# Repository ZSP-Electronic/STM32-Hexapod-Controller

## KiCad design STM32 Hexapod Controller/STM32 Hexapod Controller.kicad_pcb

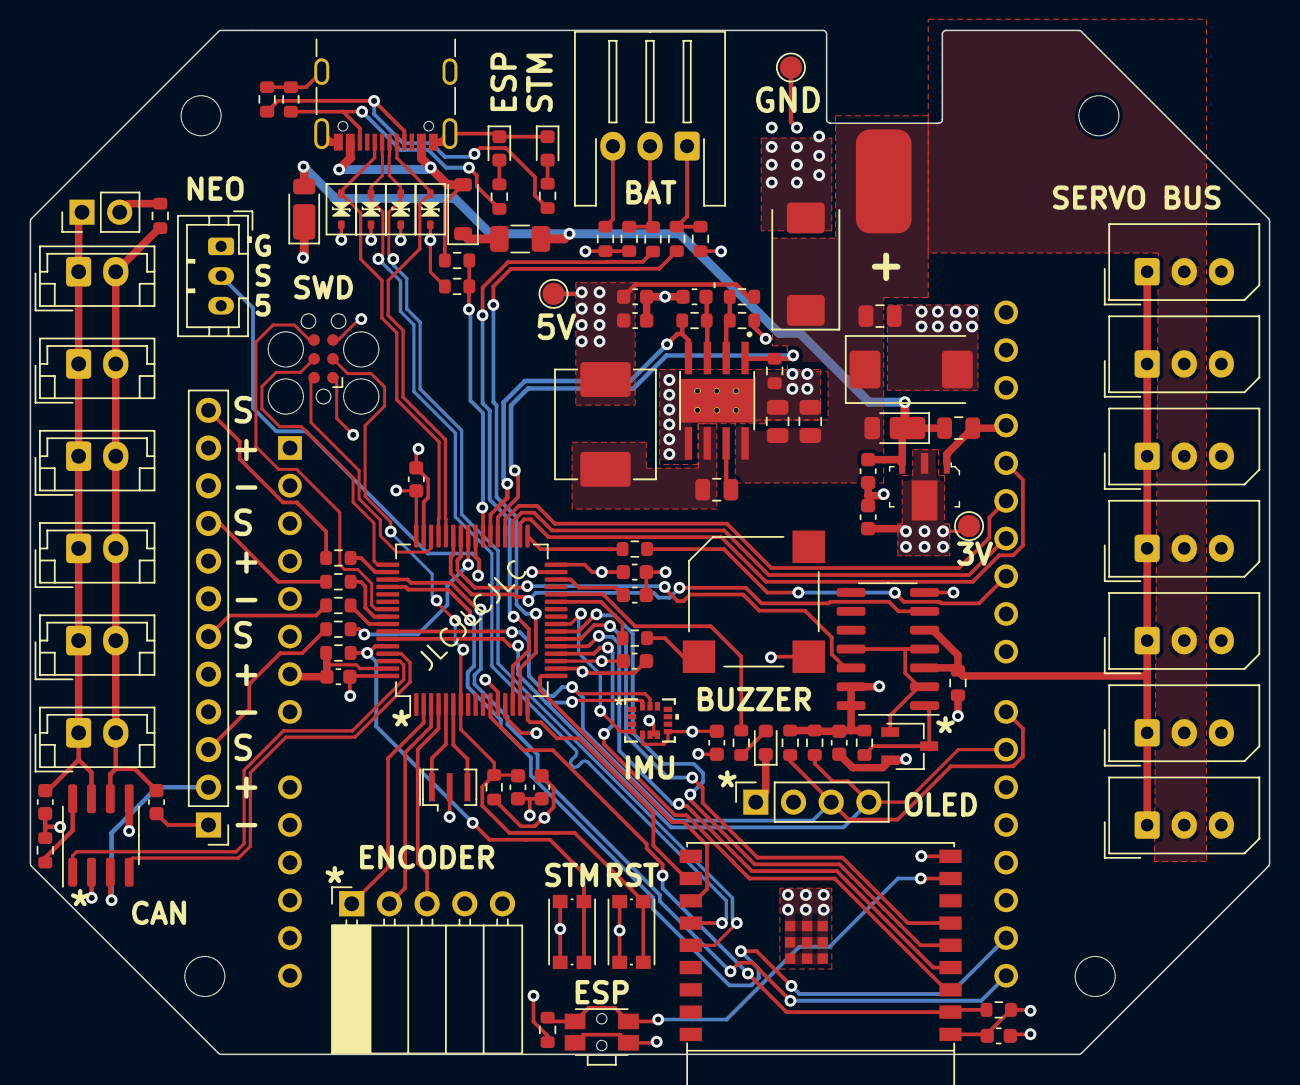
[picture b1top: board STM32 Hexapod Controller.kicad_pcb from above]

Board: 4 copper layers, 83.5 x 69.0 mm, 111 parts (1 on the bottom side), 80 nets.

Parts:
A1: Arduino_UNO_R3
BZ1: Buzzer; MagneticBuzzer_Kobitone_254-EMB84Q-RO
C1, C2: 100uF; CP_EIA-7343-31_Kemet-D
C3: 10u; C_0805_2012Metric
C4, C38, C39, C40, C41, C42, C45, C46: 10uF; C_0603_1608Metric
C6, C7, C13: 10uF; C_0805_2012Metric
C8: .1uF; C_0805_2012Metric
C9, C10, C14: 22uF; C_0603_1608Metric
C11: .47uF; C_0603_1608Metric
C12: 1uF; C_0603_1608Metric
C35, C37: 47pF; C_0603_1608Metric
C47: 1nF; C_0603_1608Metric
C48: 4.7uF; C_0603_1608Metric
D1: 1N914WT; D_SOD-123
D2: STM; LED_0603_1608Metric
D3, D4, D5, D6: DESD5V0U1BA; D_SOD-323_TVS
D7, D10: D_Small; D_PowerDI-123
D8: ESP; LED_0603_1608Metric
D9: LED; LED_0603_1608Metric
F1: Polyfuse_Small; Fuse_1206_3216Metric
H1, H2, H3, H4: MountingHole; MountingHole_2.7mm_M2.5
J1, J2, J3, J4, J5, J6, J18: Conn_01x03_Socket; Molex_SPOX_5267-03A_1x03_P2.50mm_Vertical
J7: Conn_01x03; JST_XH_S3B-XH-A-1_1x03_P2.50mm_Horizontal
J8: USB_C_Receptacle_USB2.0; USB_C_Receptacle_GCT_USB4105-xx-A_16P_TopMnt_Horizontal
J9, J10, J11, J12, J13, J14: Conn_01x02_Socket; JST_EH_B2B-EH-A_1x02_P2.50mm_Vertical
J15: Conn_ARM_SWD_TagConnect_TC2030; Tag-Connect_TC2030-IDC-FP_2x03_P1.27mm_Vertical
J16: Conn_01x02_Pin; PinHeader_1x02_P2.54mm_Vertical
J17: Conn_01x12_Pin; PinHeader_1x12_P2.54mm_Vertical
J19: Conn_01x03_Socket; JST_PH_B3B-PH-K_1x03_P2.00mm_Vertical
J20: Conn_01x05_Socket; PinSocket_1x05_P2.54mm_Horizontal
J21: Conn_01x04_Socket; PinSocket_1x04_P2.54mm_Vertical
L1: 3.3uH; L_Abracon_ASPI-0630LR
P1: CONN_002; DEAN_PCB
Q1: 2N7002AQ; TSOT-23
R1, R2, R4, R21, R25, R26, R33: 1K; R_0603_1608Metric
R3, R10: 1K5; R_0603_1608Metric
R5: DNP; R_0603_1608Metric
R6: 3K; R_0603_1608Metric
R7, R8, R18, R19, R20, R23, R28, R29, R30: 10K; R_0603_1608Metric
R9: 11K5; R_0603_1608Metric
R11: 100K; R_0603_1608Metric
R12, R13, R14, R15, R24: 100R; R_0603_1608Metric
R16, R17: 5.1K; R_0603_1608Metric
R22: 120R; R_0603_1608Metric
R31, R32: 4K7; R_0603_1608Metric
SW1, SW2: SW_Push; SW_Push_1P1T_NO_CK_KMR2
SW3: SW_Push; SW_SPST_EVQP7C
TP1, TP2, TP3: TestPoint; TestPoint_Pad_D1.5mm
U1: 74126; SOIC-14_3.9x8.7mm_P1.27mm
U2: TPS56528DDAR; IC_TPS56528DDAR
U3: AZ1117CH-3_3TRG1; TO-243AA
U4: ESP32-C3-WROOM-02
U5: STM32F446RETx; LQFP-64_10x10mm_P0.5mm
U6: TJA1051T-3; SOIC-8_3.9x4.9mm_P1.27mm
U7: LSM6DSOTR; LGA-14L_2P5X3X0P86_STM
Y1: Resonator_Small; Resonator_SMD_Murata_CSTxExxV-3Pin_3.0x1.1mm

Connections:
+3.3V: C4.1, C14.1, C38.1, C39.1, C40.1, C41.1, C42.1, C45.1, C46.1, J15.1 (VCC), J20.4, J21.2, R1.1, R2.1, R18.1, R20.1, R30.1, R31.1, R32.1, SW2.1, TP3.1, U1.13 (EN), U1.14 (VCC), U3.2 (OUT), U3.4 (VOUT), U4.1 (3V3), U5.13 (VDDA), U5.19 (VDD), U5.32 (VDD), U5.48 (VDD), U5.64 (VDD), U6.5 (VIO), U7.5 (VDDIO), U7.8 (VDD)
/+5V: A1.5 (+5V), A1.8 (VIN), C9.1, C10.1, D7.1 (K), J17.2, J17.5, J17.8, J17.11, J19.3, L1.2, R9.1, TP1.1, U6.3 (VCC)
/+12V: C1.1, C2.1, C3.1, C6.1, C7.1, D10.2 (A), J1.2, J2.2, J3.2, J4.2, J5.2, J6.2, J18.2, P1.1, U2.8 (VIN)
/BAT1: R3.1, U5.15 (PA1)
/BAT2: R6.1, U5.14 (PA0)
/CAN_HIGH: C35.2, J9.1, J10.1, J11.1, J12.1, J13.1, J14.1, J16.1, U6.7 (CANH)
/CAN_LOW: C37.1, J9.2, J10.2, J11.2, J12.2, J13.2, J14.2, R22.2, U6.6 (CANL)
/CAN_RX: U5.61 (PB8), U6.4 (RXD)
/CAN_SILENT: R23.1, U6.8 (S)
/CAN_TX: U5.62 (PB9), U6.1 (TXD)
/CS: A1.25 (D10), R12.2
/Fan: R24.2, U5.50 (PA15)
/MCU/BUZZER: R21.1, U5.27 (PB1)
/MCU/EN_CLK: J20.1, U5.2 (PC13)
/MCU/EN_DATA: J20.2, U5.3 (PC14)
/MCU/EN_SW: J20.3, U5.4 (PC15)
/MCU/ESP_BOOT: R30.2, SW3.1, U4.8 (GPIO9)
/MCU/ESP_CS: U4.3 (GPIO4/ADC1_CH4), U5.20 (PA4)
/MCU/ESP_MISO: U4.6 (GPIO7), U5.22 (PA6)
/MCU/ESP_MOSI: U4.5 (GPIO6), U5.23 (PA7)
/MCU/ESP_RST: R20.2, U4.2 (EN/CHIP_PU), U5.11 (PC3)
/MCU/ESP_RX_TX: U4.12 (GPIO21/U0TXD), U5.17 (PA3)
/MCU/ESP_SCK: U4.4 (GPIO5/ADC2_CH0), U5.21 (PA5)
/MCU/ESP_TX_RX: U4.11 (GPIO20/U0RXD), U5.16 (PA2)
/MCU/ESP_USB_D+: D5.2 (A), J8.A6 (D+), U4.14 (GPIO19/USB_D+)
/MCU/ESP_USB_D-: D3.2 (A), J8.A7 (D-), U4.13 (GPIO18/USB_D-)
/MCU/IMU_INT: U5.24 (PC4), U7.4 (INT1)
/MCU/LED: R33.1, U5.28 (PB2)
/MCU/REG_EN: R8.2, U2.1 (EN), U5.37 (PC6)
/MCU/REG_PG: R11.1, U2.4 (PG), U5.38 (PC7)
/MCU/RST: C47.1, J15.3 (~RESET), R18.2, SW1.1, U5.7 (NRST)
/MCU/STM_BOOT: R19.1, SW2.2, U5.60 (BOOT0)
/MCU/STM_INPUT: D1.2 (A), J8.A4 (VBUS1), J8.A9 (VBUS2), J8.B4 (VBUS2), J8.B9 (VBUS1), R28.1
/MCU/STM_USB_D+: D6.2 (A), J8.B6 (D+), U5.45 (PA12)
/MCU/STM_USB_D-: D4.2 (A), J8.B7 (D-), U5.44 (PA11)
/MCU/STM_USB_INPUT: R28.2, R29.1, U5.39 (PC8)
/MCU/SWD_CLK: J15.4 (SWCLK), U5.49 (PA14)
/MCU/SWD_DIO: J15.2 (SWDIO), U5.46 (PA13)
/MCU/SWD_SWO: J15.6 (SWO), U5.55 (PB3)
/MISO: A1.27 (D12), U5.36 (PB15)
/MOSI: A1.26 (D11), U5.35 (PB14)
/NEOPIXEL: J19.2, U5.40 (PC9)
/PSU/SW: C8.2, L1.1, U2.6 (SW)
/PSU/VBUS: C12.1, C13.1, D7.2 (A), D10.1 (K), F1.2, U3.3 (IN)
/RX: A1.16 (D1/TX), U5.52 (PC11)
/RX_TX: U1.6 (O), U5.43 (PA10)
/SCK: A1.28 (D13), U5.34 (PB13)
/SCL: A1.22 (D7), J21.3, R31.2, U5.58 (PB6), U7.13 (SCL)
/SDA: A1.21 (D6), J21.4, R32.2, U5.59 (PB7), U7.14 (SDA)
/Servo1: R13.2, U5.41 (PA8)
/Servo2: R14.2, U5.57 (PB5)
/Servo3: R15.2, U5.56 (PB4)
/TX: A1.15 (D0/RX), U5.51 (PC10)
/TX_RX: U1.12 (D), U5.42 (PA9)
/fanc: J17.12, R24.1
/servo1c: J17.3, R13.1
/servo2c: J17.6, R14.1
/servo3: J17.9, R15.1
GND: A1.6 (GND), A1.7 (GND), A1.29 (GND), BZ1.2 (+), C1.2, C2.2, C3.2, C4.2, C6.2, C7.2, C9.2, C10.2, C11.2, C12.2, C13.2, C14.2, C35.1, C37.2, C38.2, C39.2, C40.2, C41.2, C42.2, C45.2, C46.2, C47.2, C48.2, D2.1 (K), D3.1 (K), D4.1 (K), D5.1 (K), D6.1 (K), D8.1 (K), D9.1 (K), J1.3, J2.3, J3.3, J4.3, J5.3, J6.3, J8.A1 (GND), J8.A12 (GND), J8.B1 (GND), J8.B12 (GND), J8.S1 (SHIELD), J15.5 (GND), J17.1, J17.4, J17.7, J17.10, J18.3, J19.1, J20.5, J21.1, P1.2, Q1.2 (S), R4.1, R5.2, R7.1, R8.1, R10.2, R16.2, R17.2, R19.2, R23.2, R29.2, SW1.2, SW3.2, TP2.1, U1.7 (GND), U2.5 (GND), U2.9 (POWERPAD), U3.1 (ADJ/GND), U4.9 (GND), U4.19 (GND), U5.12 (VSSA), U5.18 (VSS), U5.31 (VSS), U5.47 (VSS), U5.63 (VSS), U6.2 (GND), U7.6 (GND), U7.7 (GND), Y1.2
unnamed: BZ1.1 (-), R21.2
unnamed: D1.1 (K), F1.1
unnamed: D2.2 (A), R25.1
unnamed: D8.2 (A), R26.1
unnamed: D9.2 (A), R33.2
unnamed: J7.1, R3.2, R4.2
unnamed: J7.2, R6.2, R7.2
unnamed: J7.3, R5.1
unnamed: J8.A5 (CC1), R17.1, R25.2
unnamed: J8.B5 (CC2), R16.1, R26.2
unnamed: J16.2, R22.1
unnamed: Q1.3 (D), R1.2, U1.1 (EN)
unnamed: Q1.1 (G), U1.2 (D), U1.4 (EN), U1.11 (O)
unnamed: C8.1, U2.7 (VBST)
unnamed: R9.2, R10.1, U2.2 (VFB)
unnamed: C11.1, R11.2, U2.3 (VREG5)
unnamed: R12.1, U5.33 (PB12)
unnamed: U5.5 (PH0), Y1.1
unnamed: U5.6 (PH1), Y1.3
unnamed: C48.1, U5.30 (VCAP_1)
servo: J1.1, J2.1, J3.1, J4.1, J5.1, J6.1, J18.1, R2.2, U1.3 (O), U1.5 (D)

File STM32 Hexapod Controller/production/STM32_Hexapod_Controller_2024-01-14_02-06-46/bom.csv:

Designator,Footprint,Quantity,Value,LCSC Part #
A1,Arduino_UNO_R3,1,Arduino_UNO_R3,
BZ1,MagneticBuzzer_Kobitone_254-EMB84Q-RO,1,Buzzer,
"C1, C2",CP_EIA-7343-31_Kemet-D,2,100uF,
"C10, C14, C9",0603,3,22uF,
C11,0603,1,.47uF,
C12,0603,1,1uF,
"C13, C6, C7",0805,3,10uF,
C3,0805,1,10u,
"C35, C37",0603,2,47pF,
"C38, C39, C4, C40, C41, C42, C45, C46",0603,8,10uF,
C47,0603,1,1nF,
C48,0603,1,4.7uF,
C8,0805,1,.1uF,
D1,D_SOD-123,1,1N914WT,
"D10, D7",D_PowerDI-123,2,D_Small,
D2,0603,1,STM,
"D3, D4, D5, D6",D_SOD-323_TVS,4,DESD5V0U1BA,
D8,0603,1,ESP,
D9,0603,1,LED,
F1,1206,1,Polyfuse_Small,
"H1, H2, H3, H4",MountingHole_2.7mm_M2.5,4,MountingHole,
"J1, J18, J2, J3, J4, J5, J6",Molex_SPOX_5267-03A_1x03_P2.50mm_Vertical,7,Conn_01x03_Socket,
"J10, J11, J12, J13, J14, J9",JST_EH_B2B-EH-A_1x02_P2.50mm_Vertical,6,Conn_01x02_Socket,
J16,PinHeader_1x02_P2.54mm_Vertical,1,Conn_01x02_Pin,
J17,PinHeader_1x12_P2.54mm_Vertical,1,Conn_01x12_Pin,
J19,JST_PH_B3B-PH-K_1x03_P2.00mm_Vertical,1,Conn_01x03_Socket,
J20,PinSocket_1x05_P2.54mm_Horizontal,1,Conn_01x05_Socket,
J21,PinSocket_1x04_P2.54mm_Vertical,1,Conn_01x04_Socket,
J7,JST_XH_S3B-XH-A-1_1x03_P2.50mm_Horizontal,1,Conn_01x03,
J8,USB_C_Receptacle_GCT_USB4105-xx-A_16P_TopMnt_Horizontal,1,USB_C_Receptacle_USB2.0,
L1,L_Abracon_ASPI-0630LR,1,3.3uH,
P1,DEAN_PCB,1,CONN_002,
Q1,TSOT-23,1,2N7002AQ,
"R1, R2, R21, R25, R26, R33, R4",0603,7,1K,
"R10, R3",0603,2,1K5,
R11,0603,1,100K,
"R12, R13, R14, R15, R24",0603,5,100R,
"R16, R17",0603,2,5.1K,
"R18, R19, R20, R23, R28, R29, R30, R7, R8",0603,9,10K,
R22,0603,1,120R,
"R31, R32",0603,2,4K7,
R6,0603,1,3K,
R9,0603,1,11K5,
"SW1, SW2",SW_Push_1P1T_NO_CK_KMR2,2,SW_Push,
SW3,SW_SPST_EVQP7C,1,SW_Push,
"TP1, TP2, TP3",TestPoint_Pad_D1.5mm,3,TestPoint,
U1,SOIC-14_3.9x8.7mm_P1.27mm,1,74126,
U2,IC_TPS56528DDAR,1,TPS56528DDAR,
U3,TO-243AA,1,AZ1117CH-3_3TRG1,AZ1117CH-3.3TRG1
U4,ESP32-C3-WROOM-02,1,ESP32-C3-WROOM-02,
U5,LQFP-64_10x10mm_P0.5mm,1,STM32F446RETx,
U6,SOIC-8_3.9x4.9mm_P1.27mm,1,TJA1051T-3,
U7,LGA-14L_2P5X3X0P86_STM,1,LSM6DSOTR,
Y1,Resonator_SMD_Murata_CSTxExxV-3Pin_3.0x1.1mm,1,Resonator_Small,

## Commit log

2024-01-14 PCB Version 1.0
